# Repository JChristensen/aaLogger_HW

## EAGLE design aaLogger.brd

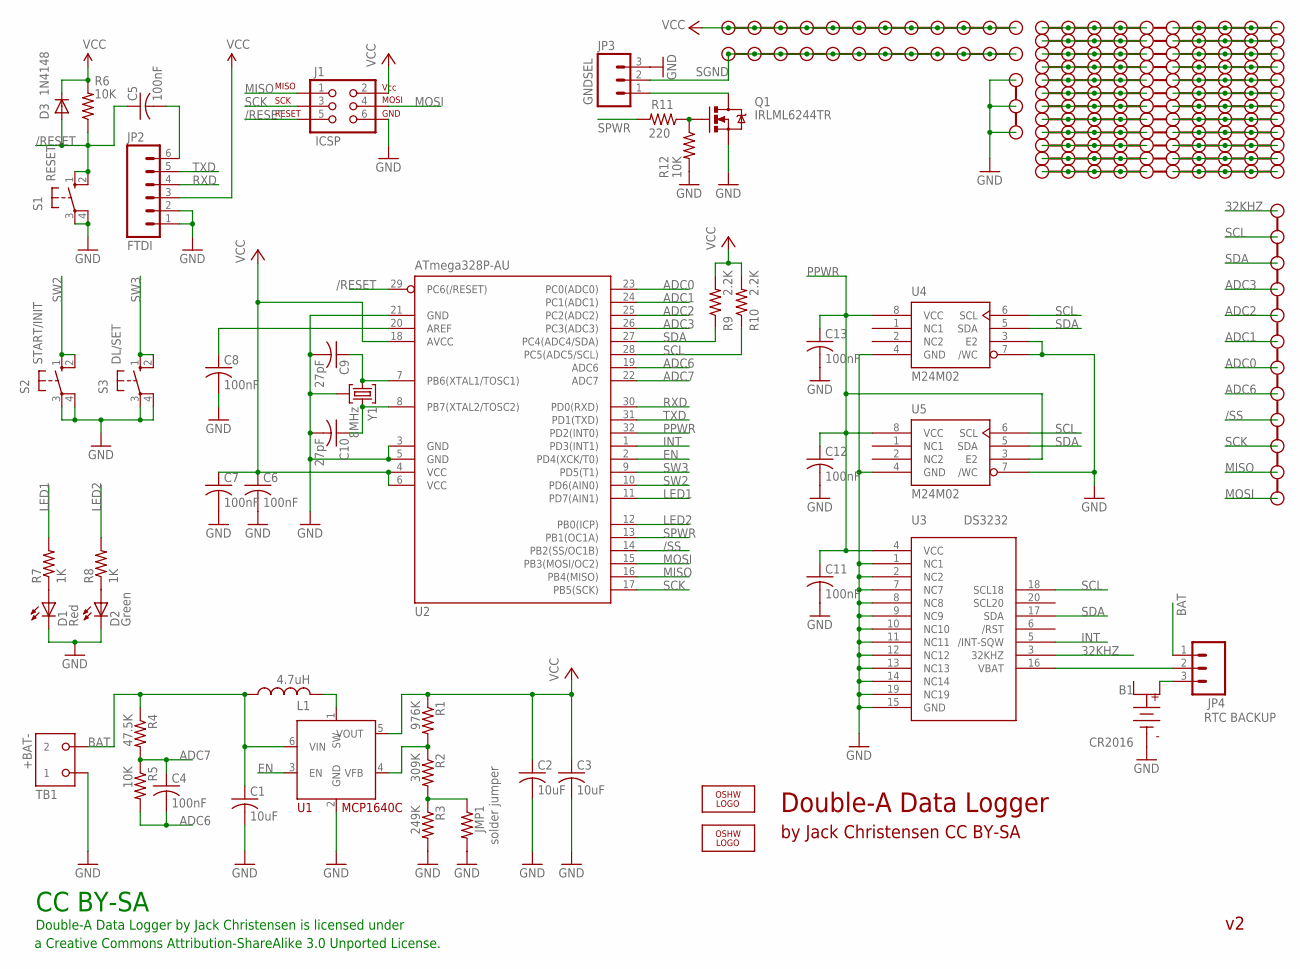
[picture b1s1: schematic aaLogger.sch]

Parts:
B1: CR2016; BAT-HLD-002-SMT
C1, C2, C3: 10uF; M0805
C4, C5, C6, C7, C8, C11, C12, C13: 100nF; M0805
C9, C10: 27pF; M0805
D1: Red; CHIPLED_1206
D2: Green; CHIPLED_1206
D3: 1N4148; SOD-323F
J1: ICSP; 2X3_LOCK
JMP1: solder jumper; M0805
JP1: PROTO-12NR; PROTO-12-NR
JP2: FTDI; 1X06_LOCK
JP3: GNDSEL; 1X03_LOCK
JP4: RTC BACKUP; 1X03_LOCK
L1: 4.7uH; NRS5020
LOGO1, LOGO2: OSHW_LOGO_8MILX0150-NT; OSHW_8X150_NOTEXT
PR1, PR2, PR3, PR4, PR5, PR6, PR7, PR8, PR9, PR10, PR11, PR12: PROTO-10
PR13: PROTO-3
Q1: IRLML6244TR; SOT23
R1: 976K; M0805
R2: 309K; M0805
R3: 249K; M0805
R4: 47.5K; M0805
R5, R6, R12: 10K; M0805
R7, R8: 1K; M0805
R9, R10: 2.2K; M0805
R11: 220; M0805
S1: RESET; B3F-10XXOCT
S2: START/INIT; B3F-10XXOCT
S3: DL/SET; B3F-10XXOCT
TB1: +BAT-; OST-TB-2-3.5MM
U1: MCP1640C; SOT23-6
U2: ATmega328P-AU; TQFP32-08
U3: DS3232; SO20W
U4, U5: M24M02; SO08
U$1, U$2: PROTO-12PROTO; PROTO-12
Y1: 8MHz; RESONATOR

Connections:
32KHZ: JP1.1, U3.3 (32KHZ)
/RESET: C5.1, D3.A, J1.5, R6.1, S1.1 (S), S1.2 (S1), U2.29 (PC6(/RESET))
/SS: JP1.9, U2.14 (PB2(SS/OC1B))
ADC0: JP1.7, U2.23 (PC0(ADC0))
ADC1: JP1.6, U2.24 (PC1(ADC1))
ADC2: JP1.5, U2.25 (PC2(ADC2))
ADC3: JP1.4, U2.26 (PC3(ADC3))
ADC6: C4.2, JP1.8, R5.2, U2.19 (ADC6)
ADC7: C4.1, R4.2, R5.1, U2.22 (ADC7)
BAT: C1.1, JP4.1, L1.P$1 (1), R4.1, TB1.P$2 (2), U1.6 (VIN)
EN: U1.3 (EN), U2.2 (PD4(XCK/T0))
GND: B1.NEG (B-), C1.2, C2.2, C3.2, C6.2, C7.2, C8.2, C9.2, C10.2, C11.2, C12.2, C13.2, D1.C, D2.C, J1.6, JMP1.2, JP2.1, JP2.2, JP3.3, PR13.1, PR13.2, PR13.3, Q1.2 (S), R3.2, R12.2, S1.3, S1.4 (P1), S2.3, S2.4 (P1), S3.3, S3.4 (P1), TB1.P$1 (1), U1.2 (GND), U2.3 (GND), U2.5 (GND), U2.21 (GND), U3.1 (NC1), U3.2 (NC2), U3.7 (NC7), U3.8 (NC8), U3.9 (NC9), U3.10 (NC10), U3.11 (NC11), U3.12 (NC12), U3.13 (NC13), U3.14 (NC14), U3.15 (GND), U3.19 (NC19), U4.3 (E2), U4.4 (GND), U4.7 (/WC), U5.4 (GND), U5.7 (/WC), Y1.2
INT: U2.1 (PD3(INT1)), U3.5 (/INT-SQW)
LED1: R7.2, U2.11 (PD7(AIN1))
LED2: R8.2, U2.12 (PB0(ICP))
MISO: J1.1, JP1.11, U2.16 (PB4(MISO))
MOSI: J1.4, JP1.12, U2.15 (PB3(MOSI/OC2))
unnamed: B1.POS1, JP4.3
unnamed: D1.A, R7.1
unnamed: D2.A, R8.1
unnamed: PR1.6, PR1.7, PR1.8, PR1.9, PR1.10
unnamed: PR5.6, PR5.7, PR5.8, PR5.9, PR5.10
unnamed: R1.2, R2.1, U1.4 (VFB)
unnamed: L1.P$2 (2), U1.1 (SW)
unnamed: C9.1, U2.7 (PB6(XTAL1/TOSC1)), Y1.1
unnamed: PR2.6, PR2.7, PR2.8, PR2.9, PR2.10
unnamed: PR3.6, PR3.7, PR3.8, PR3.9, PR3.10
unnamed: C10.1, U2.8 (PB7(XTAL2/TOSC2)), Y1.3
unnamed: JMP1.1, R2.2, R3.1
unnamed: C8.1, U2.20 (AREF)
unnamed: PR4.6, PR4.7, PR4.8, PR4.9, PR4.10
unnamed: PR6.6, PR6.7, PR6.8, PR6.9, PR6.10
unnamed: PR7.1, PR7.2, PR7.3, PR7.4, PR7.5
unnamed: PR8.1, PR8.2, PR8.3, PR8.4, PR8.5
unnamed: PR9.1, PR9.2, PR9.3, PR9.4, PR9.5
unnamed: PR10.1, PR10.2, PR10.3, PR10.4, PR10.5
unnamed: PR11.1, PR11.2, PR11.3, PR11.4, PR11.5
unnamed: PR12.1, PR12.2, PR12.3, PR12.4, PR12.5
unnamed: PR1.1, PR1.2, PR1.3, PR1.4, PR1.5
unnamed: PR2.1, PR2.2, PR2.3, PR2.4, PR2.5
unnamed: Q1.1 (G), R11.1, R12.1
unnamed: PR3.1, PR3.2, PR3.3, PR3.4, PR3.5
unnamed: PR4.1, PR4.2, PR4.3, PR4.4, PR4.5
unnamed: PR6.1, PR6.2, PR6.3, PR6.4, PR6.5
unnamed: PR7.6, PR7.7, PR7.8, PR7.9, PR7.10
unnamed: PR5.1, PR5.2, PR5.3, PR5.4, PR5.5
unnamed: PR8.6, PR8.7, PR8.8, PR8.9, PR8.10
unnamed: PR9.6, PR9.7, PR9.8, PR9.9, PR9.10
unnamed: PR10.6, PR10.7, PR10.8, PR10.9, PR10.10
unnamed: PR11.6, PR11.7, PR11.8, PR11.9, PR11.10
unnamed: PR12.6, PR12.7, PR12.8, PR12.9, PR12.10
unnamed: JP4.2, U3.16 (VBAT)
unnamed: JP3.1, Q1.3 (D)
PPWR: C11.1, C12.1, C13.1, U2.32 (PD2(INT0)), U3.4 (VCC), U4.8 (VCC), U5.3 (E2), U5.8 (VCC)
RST: C5.2, JP2.6
RXD: JP2.4, U2.30 (PD0(RXD))
SCK: J1.3, JP1.10, U2.17 (PB5(SCK))
SCL: JP1.2, R10.1, U2.28 (PC5(ADC5/SCL)), U3.18 (SCL18), U4.6 (SCL), U5.6 (SCL)
SDA: JP1.3, R9.1, U2.27 (PC4(ADC4/SDA)), U3.17 (SDA), U4.5 (SDA), U5.5 (SDA)
SGND: JP3.2, U$2.1, U$2.2, U$2.3, U$2.4, U$2.5, U$2.6, U$2.7, U$2.8, U$2.9, U$2.10, U$2.11, U$2.12
SPWR: R11.2, U2.13 (PB1(OC1A))
SW2: S2.1 (S), S2.2 (S1), U2.10 (PD6(AIN0))
SW3: S3.1 (S), S3.2 (S1), U2.9 (PD5(T1))
TXD: JP2.5, U2.31 (PD1(TXD))
VCC: C2.1, C3.1, C6.1, C7.1, D3.K, J1.2, JP2.3, R1.1, R6.2, R9.2, R10.2, U1.5 (VOUT), U2.4 (VCC), U2.6 (VCC), U2.18 (AVCC), U$1.1, U$1.2, U$1.3, U$1.4, U$1.5, U$1.6, U$1.7, U$1.8, U$1.9, U$1.10, U$1.11, U$1.12

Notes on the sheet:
Double-A Data Logger
by Jack Christensen CC BY-SA
Double-A Data Logger by Jack Christensen is licensed under
CC BY-SA
a Creative Commons Attribution-ShareAlike 3.0 Unported License.

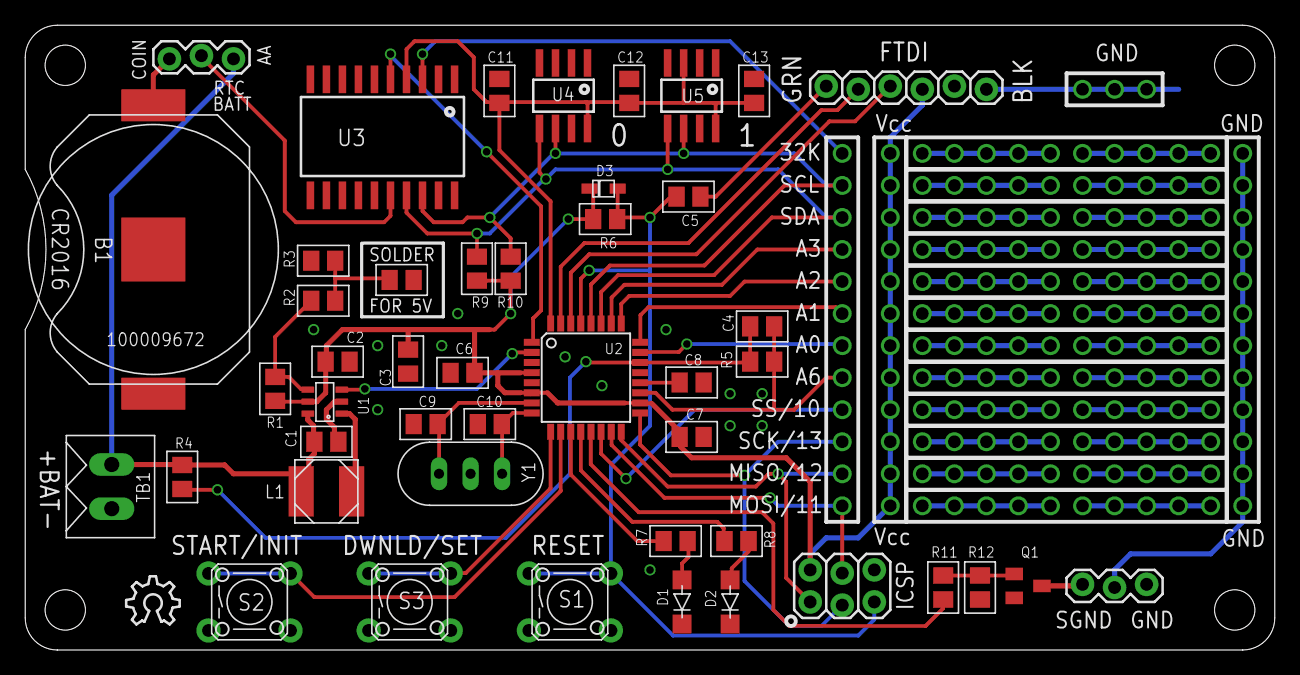
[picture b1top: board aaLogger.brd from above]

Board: 2 copper layers, 99.1 x 49.5 mm, 64 parts (1 on the bottom side), 65 nets.

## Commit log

2013-02-12 Initial commit, 3.5" board length.
2013-03-14 Near final.
2013-03-16 v1 as sent to iTead.
2013-03-29 Remove R11, not needed. Reroute 32K, move RTC slightly.
2013-04-01 Rename resistors. Tweak schematic layout, titles. Put github URL on bottom of board.

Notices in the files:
aaLogger.brd:
CC BY-SA jc 0313 v2
